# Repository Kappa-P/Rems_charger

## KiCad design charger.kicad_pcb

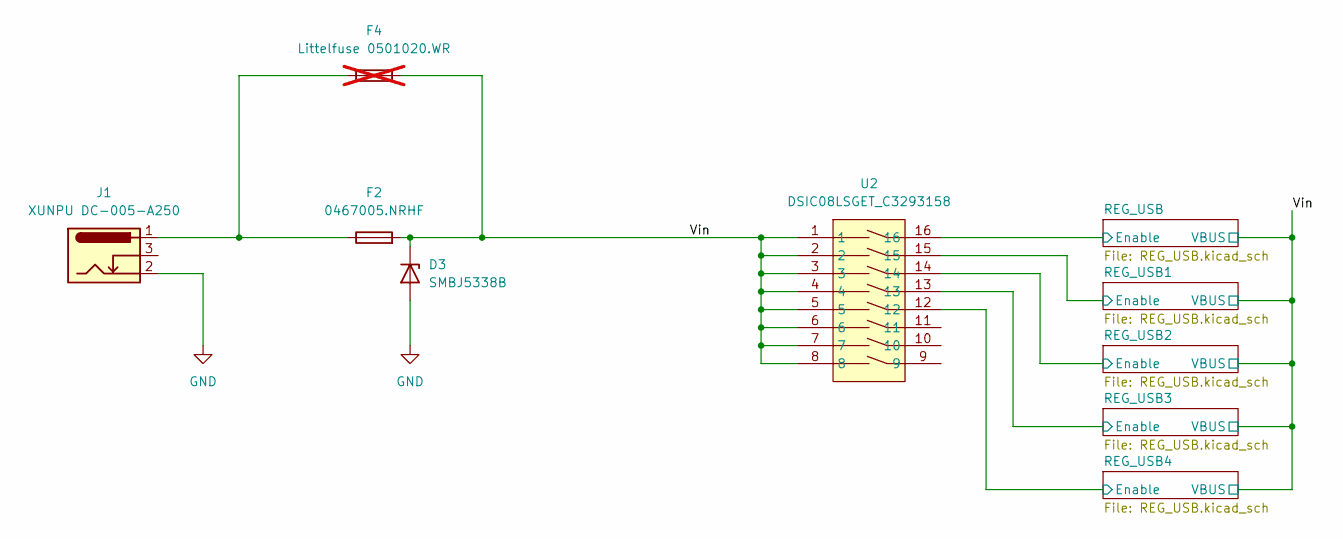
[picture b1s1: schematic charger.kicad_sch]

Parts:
D3: SMBJ5338B; SMB_L4.6-W3.6-LS5.4-RD
F2: 0467005.NRHF; F0603
F4: Littelfuse 0501020.WR; F1206; not fitted
J1: XUNPU DC-005-A250; DC-IN-TH_DC-005-A250
U2: DSIC08LSGET_C3293158; SW-SMD_DSIC08LSGET; LCSC Part C3293158

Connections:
/REG_USB1/Enable: U2.15; also elsewhere on the board
/REG_USB2/Enable: U2.14; also elsewhere on the board
/REG_USB3/Enable: U2.13; also elsewhere on the board
/REG_USB4/Enable: U2.12; also elsewhere on the board
/REG_USB/Enable: U2.16; also elsewhere on the board
/Vin: D3.1 (K), F2.2, F4.2, U2.1, U2.2, U2.3, U2.4, U2.5, U2.6, U2.7, U2.8; also elsewhere on the board
GND: D3.2 (A), J1.2; also elsewhere on the board
unnamed: F2.1, F4.1, J1.1

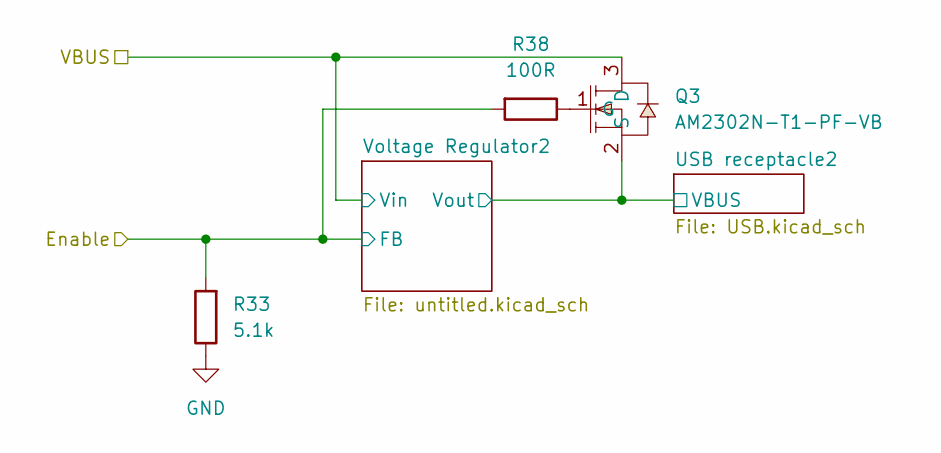
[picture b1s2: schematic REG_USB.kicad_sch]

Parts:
Q3: AM2302N-T1-PF-VB; SOT-23-3_L2.9-W1.3-P1.90-LS2.4-BR; LCSC Part C6705248
R33: 5.1k; R_0603_1608Metric_Pad0.98x0.95mm_HandSolder
R38: 100R; R_0603_1608Metric_Pad0.98x0.95mm_HandSolder

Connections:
/REG_USB1/Enable: R33.2, R38.2; also elsewhere on the board
/REG_USB1/USB receptacle2/VBUS: Q3.2 (S); also elsewhere on the board
/Vin: Q3.3 (D); also elsewhere on the board
GND: R33.1; also elsewhere on the board
unnamed: Q3.1 (G), R38.1

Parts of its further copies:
Q2, Q4, Q5, Q6: AM2302N-T1-PF-VB; SOT-23-3_L2.9-W1.3-P1.90-LS2.4-BR; LCSC Part C6705248
R34, R35, R36, R37: 5.1k; R_0603_1608Metric_Pad0.98x0.95mm_HandSolder
R39, R40, R41, R42: 100R; R_0603_1608Metric_Pad0.98x0.95mm_HandSolder

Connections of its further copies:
/REG_USB2/Enable: R35.2, R40.2; also elsewhere on the board
/REG_USB2/USB receptacle2/VBUS: Q4.2 (S); also elsewhere on the board
/REG_USB3/Enable: R36.2, R41.2; also elsewhere on the board
/REG_USB3/USB receptacle2/VBUS: Q5.2 (S); also elsewhere on the board
/REG_USB4/Enable: R37.2, R42.2; also elsewhere on the board
/REG_USB4/USB receptacle2/VBUS: Q6.2 (S); also elsewhere on the board
/REG_USB/Enable: R34.2, R39.2; also elsewhere on the board
/REG_USB/USB receptacle2/VBUS: Q2.2 (S); also elsewhere on the board
/Vin: Q2.3 (D), Q4.3 (D), Q5.3 (D), Q6.3 (D); also elsewhere on the board
GND: R34.1, R35.1, R36.1, R37.1; also elsewhere on the board
unnamed: Q2.1 (G), R39.1
unnamed: Q4.1 (G), R40.1
unnamed: Q5.1 (G), R41.1
unnamed: Q6.1 (G), R42.1

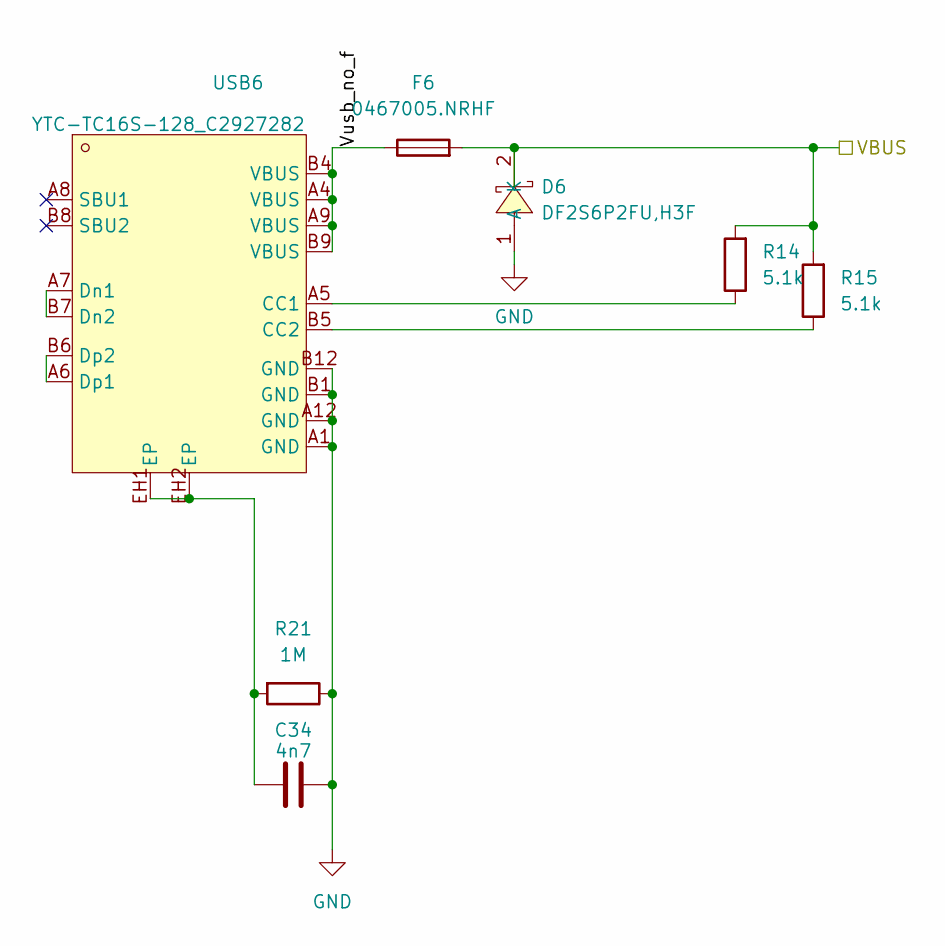
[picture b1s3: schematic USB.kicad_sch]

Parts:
C34: 4n7; C_0603_1608Metric_Pad1.08x0.95mm_HandSolder
D6: DF2S6P2FU,H3F; USC_L1.7-W1.3-LS2.5-R-RD; LCSC Part C1974448
F6: 0467005.NRHF; F0603
R14, R15: 5.1k; R_0603_1608Metric_Pad0.98x0.95mm_HandSolder
R21: 1M; R_0603_1608Metric_Pad0.98x0.95mm_HandSolder
USB6: YTC-TC16S-128_C2927282; TYPE-C-SMD_YTC-TC16S-128; LCSC Part C2927282

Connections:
/REG_USB/USB receptacle2/VBUS: D6.2 (K), F6.2, R14.2, R15.2; also elsewhere on the board
/REG_USB/USB receptacle2/Vusb_no_f: F6.1, USB6.A4 (VBUS), USB6.A9 (VBUS), USB6.B4 (VBUS), USB6.B9 (VBUS)
GND: C34.2, D6.1 (A), R21.1, USB6.A1 (GND), USB6.A12 (GND), USB6.B1 (GND), USB6.B12 (GND); also elsewhere on the board
unnamed: C34.1, R21.2, USB6.EH1 (EP), USB6.EH2 (EP)
unnamed: R14.1, USB6.A5 (CC1)
unnamed: R15.1, USB6.B5 (CC2)
unnamed: USB6.A7 (Dn1), USB6.B7 (Dn2)
unnamed: USB6.A6 (Dp1), USB6.B6 (Dp2)

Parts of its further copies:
C42, C50, C58, C59: 4n7; C_0603_1608Metric_Pad1.08x0.95mm_HandSolder
D8, D10, D12, D14: DF2S6P2FU,H3F; USC_L1.7-W1.3-LS2.5-R-RD; LCSC Part C1974448
F7, F8, F9, F10: 0467005.NRHF; F0603
R18, R19, R22, R23, R26, R27, R30, R31: 5.1k; R_0603_1608Metric_Pad0.98x0.95mm_HandSolder
R25, R29, R43, R44: 1M; R_0603_1608Metric_Pad0.98x0.95mm_HandSolder
USB7, USB8, USB9, USB10: YTC-TC16S-128_C2927282; TYPE-C-SMD_YTC-TC16S-128; LCSC Part C2927282

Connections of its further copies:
/REG_USB1/USB receptacle2/VBUS: D8.2 (K), F7.2, R18.2, R19.2; also elsewhere on the board
/REG_USB1/USB receptacle2/Vusb_no_f: F7.1, USB7.A4 (VBUS), USB7.A9 (VBUS), USB7.B4 (VBUS), USB7.B9 (VBUS)
/REG_USB2/USB receptacle2/VBUS: D10.2 (K), F8.2, R22.2, R23.2; also elsewhere on the board
/REG_USB2/USB receptacle2/Vusb_no_f: F8.1, USB8.A4 (VBUS), USB8.A9 (VBUS), USB8.B4 (VBUS), USB8.B9 (VBUS)
/REG_USB3/USB receptacle2/VBUS: D12.2 (K), F9.2, R26.2, R27.2; also elsewhere on the board
/REG_USB3/USB receptacle2/Vusb_no_f: F9.1, USB9.A4 (VBUS), USB9.A9 (VBUS), USB9.B4 (VBUS), USB9.B9 (VBUS)
/REG_USB4/USB receptacle2/VBUS: D14.2 (K), F10.2, R30.2, R31.2; also elsewhere on the board
/REG_USB4/USB receptacle2/Vusb_no_f: F10.1, USB10.A4 (VBUS), USB10.A9 (VBUS), USB10.B4 (VBUS), USB10.B9 (VBUS)
GND: C42.2, C50.2, C58.2, C59.2, D8.1 (A), D10.1 (A), D12.1 (A), D14.1 (A), R25.1, R29.1, R43.1, R44.1, USB7.A1 (GND), USB7.A12 (GND), USB7.B1 (GND), USB7.B12 (GND), USB8.A1 (GND), USB8.A12 (GND), USB8.B1 (GND), USB8.B12 (GND), USB9.A1 (GND), USB9.A12 (GND), USB9.B1 (GND), USB9.B12 (GND), USB10.A1 (GND), USB10.A12 (GND), USB10.B1 (GND), USB10.B12 (GND); also elsewhere on the board
unnamed: C42.1, R25.2, USB7.EH1 (EP), USB7.EH2 (EP)
unnamed: C50.1, R29.2, USB8.EH1 (EP), USB8.EH2 (EP)
unnamed: C58.1, R43.2, USB9.EH1 (EP), USB9.EH2 (EP)
unnamed: C59.1, R44.2, USB10.EH1 (EP), USB10.EH2 (EP)
unnamed: R18.1, USB7.A5 (CC1)
unnamed: R19.1, USB7.B5 (CC2)
unnamed: USB7.A7 (Dn1), USB7.B7 (Dn2)
unnamed: USB7.A6 (Dp1), USB7.B6 (Dp2)
unnamed: R22.1, USB8.A5 (CC1)
unnamed: R23.1, USB8.B5 (CC2)
unnamed: USB8.A7 (Dn1), USB8.B7 (Dn2)
unnamed: USB8.A6 (Dp1), USB8.B6 (Dp2)
unnamed: R26.1, USB9.A5 (CC1)
unnamed: R27.1, USB9.B5 (CC2)
unnamed: USB9.A7 (Dn1), USB9.B7 (Dn2)
unnamed: USB9.A6 (Dp1), USB9.B6 (Dp2)
unnamed: R30.1, USB10.A5 (CC1)
unnamed: R31.1, USB10.B5 (CC2)
unnamed: USB10.A7 (Dn1), USB10.B7 (Dn2)
unnamed: USB10.A6 (Dp1), USB10.B6 (Dp2)

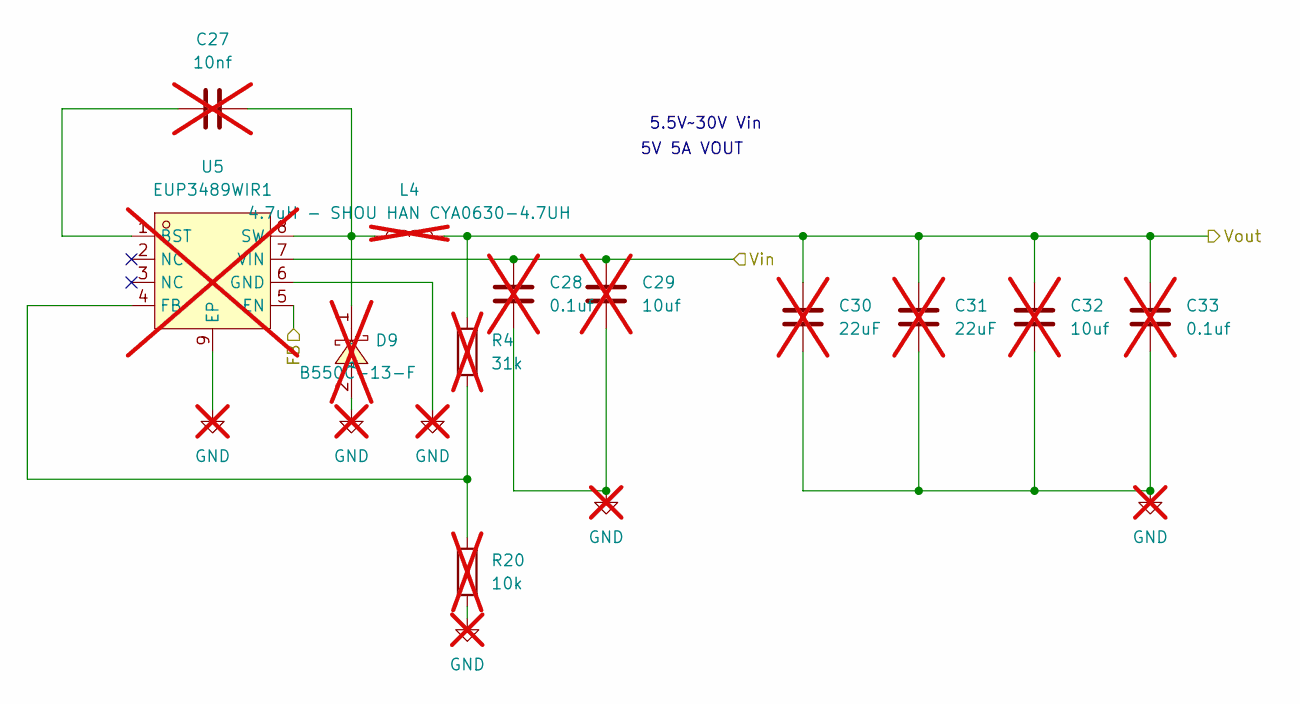
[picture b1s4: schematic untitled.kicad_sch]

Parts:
C27: 10nf; C_0603_1608Metric_Pad1.08x0.95mm_HandSolder; not fitted
C28, C33: 0.1uf; C_0603_1608Metric_Pad1.08x0.95mm_HandSolder; not fitted
C29, C32: 10uf; C_0805_2012Metric_Pad1.18x1.45mm_HandSolder; not fitted
C30, C31: 22uF; C_0805_2012Metric_Pad1.18x1.45mm_HandSolder; not fitted
D9: B550C-13-F; SMC_L6.9-W5.9-LS7.9-RD; LCSC Part C134461; not fitted
L4: 4.7uH - SHOU HAN CYA0630-4.7UH; IND-SMD_L7.2-W6.6_GPSR07X0; not fitted
R4: 31k; R_0603_1608Metric_Pad0.98x0.95mm_HandSolder; not fitted
R20: 10k; R_0603_1608Metric_Pad0.98x0.95mm_HandSolder; not fitted
U5: EUP3489WIR1; ESOP-8_L4.9-W3.9-P1.27-LS6.0-BL-EP; LCSC Part C1509135; not fitted

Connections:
/REG_USB1/Enable: U5.5 (EN); also elsewhere on the board
/REG_USB1/USB receptacle2/VBUS: C30.1, C31.1, C32.1, C33.1, L4.2, R4.1; also elsewhere on the board
/Vin: C28.1, C29.1, U5.7 (VIN); also elsewhere on the board
GND: C28.2, C29.2, C30.2, C31.2, C32.2, C33.2, D9.2 (A), R20.2, U5.6 (GND), U5.9 (EP); also elsewhere on the board
unnamed: C27.2, D9.1 (C), L4.1, U5.8 (SW)
unnamed: C27.1, U5.1 (BST)
unnamed: R4.2, R20.1, U5.4 (FB)

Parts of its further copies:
C19, C35, C43, C51: 10nf; C_0603_1608Metric_Pad1.08x0.95mm_HandSolder; not fitted
C20, C25, C36, C41, C44, C49, C52, C57: 0.1uf; C_0603_1608Metric_Pad1.08x0.95mm_HandSolder; not fitted
C21, C24, C37, C40, C45, C48, C53, C56: 10uf; C_0805_2012Metric_Pad1.18x1.45mm_HandSolder; not fitted
C22, C23, C38, C39, C46, C47, C54, C55: 22uF; C_0805_2012Metric_Pad1.18x1.45mm_HandSolder; not fitted
D7, D11, D13, D15: B550C-13-F; SMC_L6.9-W5.9-LS7.9-RD; LCSC Part C134461; not fitted
L3, L5, L6, L7: 4.7uH - SHOU HAN CYA0630-4.7UH; IND-SMD_L7.2-W6.6_GPSR07X0; not fitted
R3, R9, R10, R11: 31k; R_0603_1608Metric_Pad0.98x0.95mm_HandSolder; not fitted
R16, R24, R28, R32: 10k; R_0603_1608Metric_Pad0.98x0.95mm_HandSolder; not fitted
U4, U6, U7, U8: EUP3489WIR1; ESOP-8_L4.9-W3.9-P1.27-LS6.0-BL-EP; LCSC Part C1509135; not fitted

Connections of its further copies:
/REG_USB2/Enable: U6.5 (EN); also elsewhere on the board
/REG_USB2/USB receptacle2/VBUS: C38.1, C39.1, C40.1, C41.1, L5.2, R9.1; also elsewhere on the board
/REG_USB3/Enable: U7.5 (EN); also elsewhere on the board
/REG_USB3/USB receptacle2/VBUS: C46.1, C47.1, C48.1, C49.1, L6.2, R10.1; also elsewhere on the board
/REG_USB4/Enable: U8.5 (EN); also elsewhere on the board
/REG_USB4/USB receptacle2/VBUS: C54.1, C55.1, C56.1, C57.1, L7.2, R11.1; also elsewhere on the board
/REG_USB/Enable: U4.5 (EN); also elsewhere on the board
/REG_USB/USB receptacle2/VBUS: C22.1, C23.1, C24.1, C25.1, L3.2, R3.1; also elsewhere on the board
/Vin: C20.1, C21.1, C36.1, C37.1, C44.1, C45.1, C52.1, C53.1, U4.7 (VIN), U6.7 (VIN), U7.7 (VIN), U8.7 (VIN); also elsewhere on the board
GND: C20.2, C21.2, C22.2, C23.2, C24.2, C25.2, C36.2, C37.2, C38.2, C39.2, C40.2, C41.2, C44.2, C45.2, C46.2, C47.2, C48.2, C49.2, C52.2, C53.2, C54.2, C55.2, C56.2, C57.2, D7.2 (A), D11.2 (A), D13.2 (A), D15.2 (A), R16.2, R24.2, R28.2, R32.2, U4.6 (GND), U4.9 (EP), U6.6 (GND), U6.9 (EP), U7.6 (GND), U7.9 (EP), U8.6 (GND), U8.9 (EP); also elsewhere on the board
unnamed: C19.2, D7.1 (C), L3.1, U4.8 (SW)
unnamed: C35.2, D11.1 (C), L5.1, U6.8 (SW)
unnamed: C43.2, D13.1 (C), L6.1, U7.8 (SW)
unnamed: C51.2, D15.1 (C), L7.1, U8.8 (SW)
unnamed: C19.1, U4.1 (BST)
unnamed: R3.2, R16.1, U4.4 (FB)
unnamed: C35.1, U6.1 (BST)
unnamed: R9.2, R24.1, U6.4 (FB)
unnamed: C43.1, U7.1 (BST)
unnamed: R10.2, R28.1, U7.4 (FB)
unnamed: C51.1, U8.1 (BST)
unnamed: R11.2, R32.1, U8.4 (FB)

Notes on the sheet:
5.5V~30V Vin
5V 5A VOUT

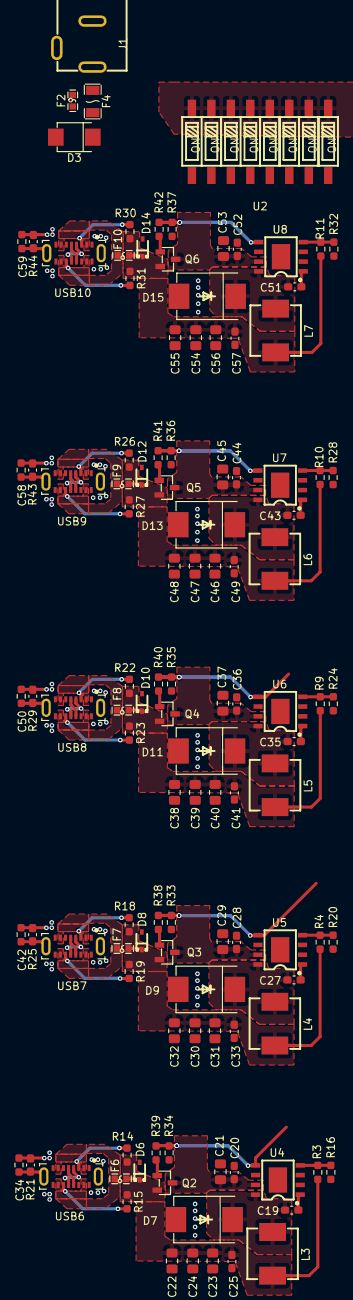
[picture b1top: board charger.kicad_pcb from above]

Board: 2 copper layers, 115 parts (0 on the bottom side), 63 nets.

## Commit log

2025-08-31 finished getting footprints and started layout
2025-09-22 sarted routing of the usb circuitry, almost finished it
2025-10-05 routing and layout done except spacing and final power route
